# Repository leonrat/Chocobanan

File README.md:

# Chocobanan
An alice-like 40% split keyboard

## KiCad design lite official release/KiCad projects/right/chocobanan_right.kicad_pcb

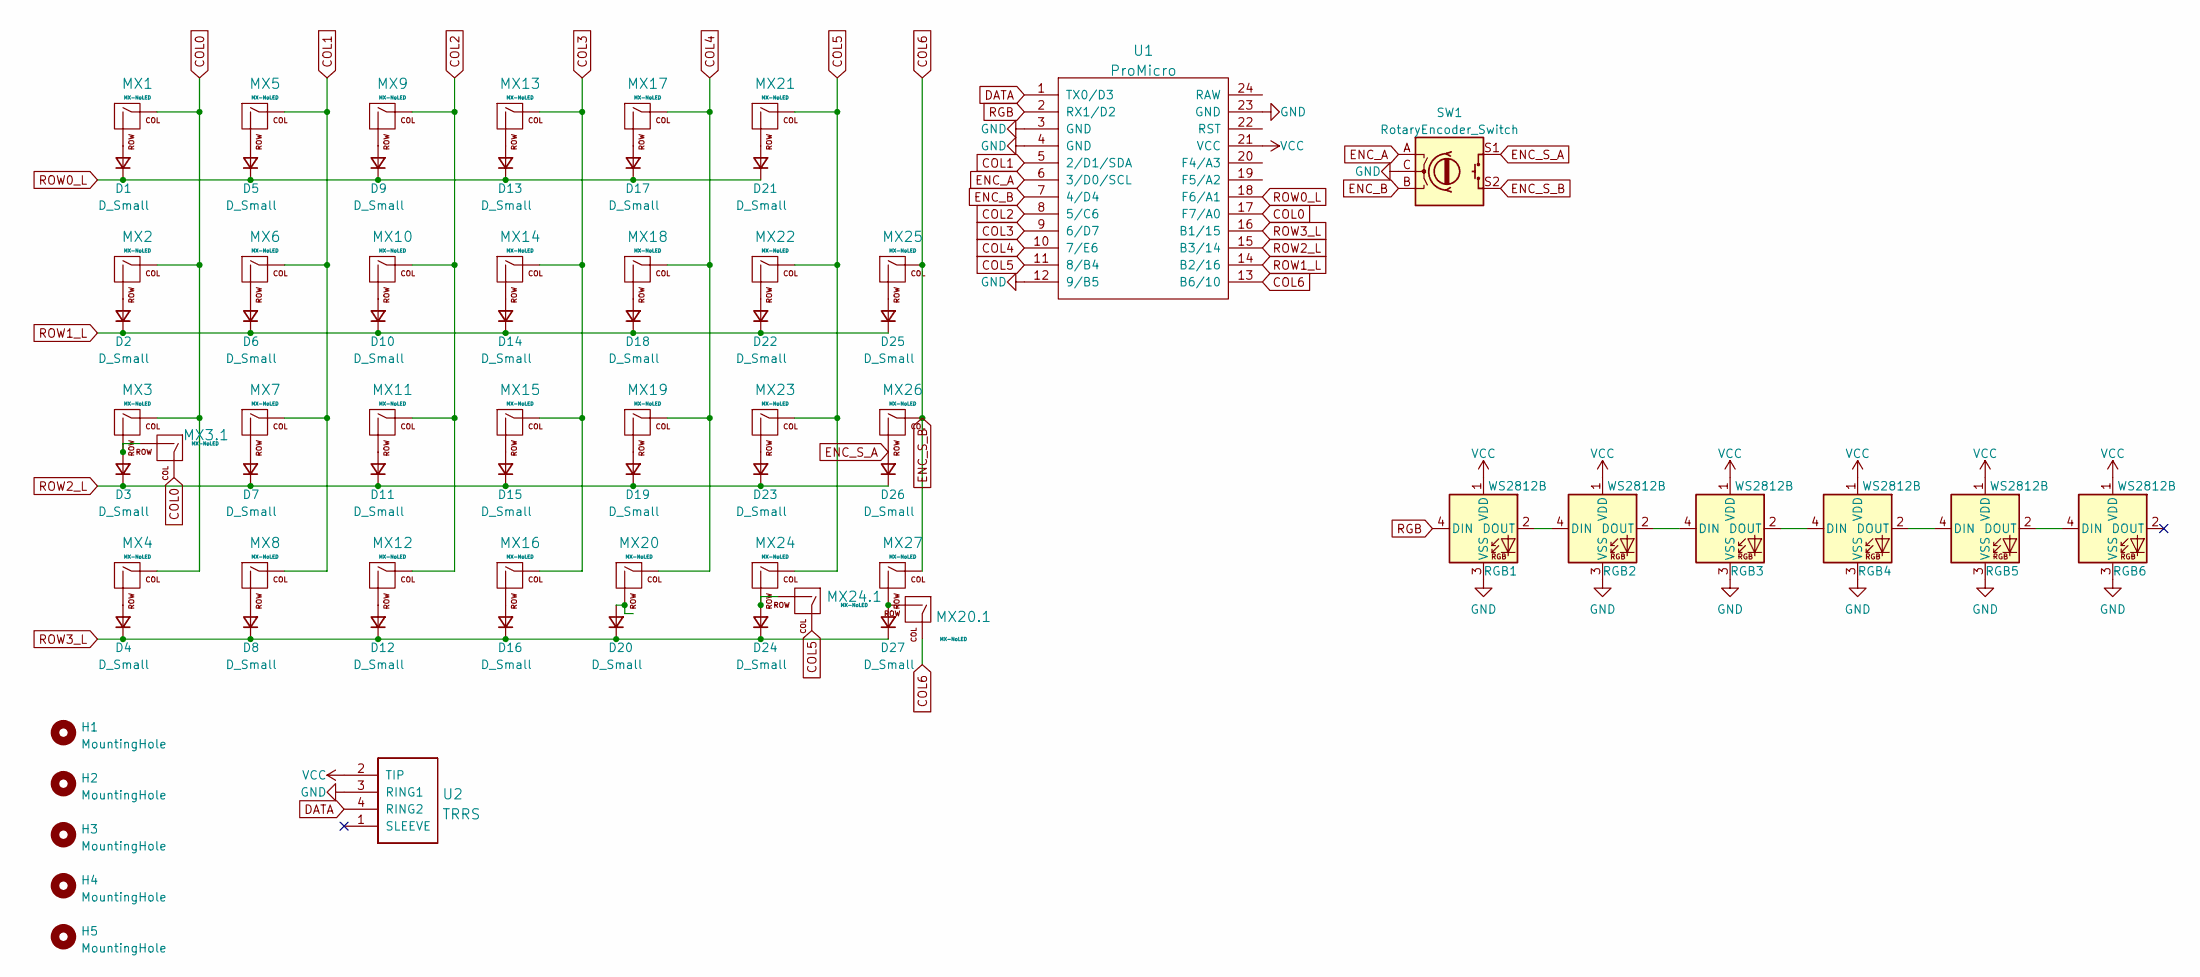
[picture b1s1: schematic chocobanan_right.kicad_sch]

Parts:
D1, D2, D3, D4, D5, D6, D7, D8, D9, D10, D11, D12, D13, D14, D15, D16, D17, D18, D19, D20, D21, D22, D23, D24, D25, D26, D27: D_Small; D3_TH_SMD_only_back
H1, H2, H3, H4, H5: MountingHole; MountingHole_2.1mm
MX1, MX20.1: MX-NoLED; MXOnly-2U-NoLED
MX2: MX-NoLED; MXOnly-2.25U-NoLED
MX3, MX24: MX-NoLED; MXOnly-1.75U-NoLED
MX3.1: MX-NoLED; MXOnly-2.75U-NoLED
MX4: MX-NoLED; MXOnly-1.25U-NoLED
MX5, MX6, MX7, MX8, MX9, MX10, MX11, MX12, MX13, MX14, MX15, MX16, MX17, MX18, MX19, MX20, MX21, MX22, MX23, MX25, MX26, MX27: MX-NoLED; MXOnly-1U-NoLED
MX24.1: MX-NoLED; MXOnly-2.75U-ReversedStabilizers-NoLED
RGB1, RGB2, RGB3, RGB4, RGB5, RGB6: WS2812B; LED_WS2812B-PLCC4
SW1: RotaryEncoder_Switch; RotaryEncoder_EC11_Switch
U1: ProMicro; ArduinoProMicro_centered
U2: TRRS; TRRS-PJ-320A

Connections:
COL0: MX1.1 (COL), MX2.1 (COL), MX3.1 (COL), MX3.1.1 (COL), MX4.1 (COL), U1.17 (F7/A0)
COL1: MX5.1 (COL), MX6.1 (COL), MX7.1 (COL), MX8.1 (COL), U1.5 (2/D1/SDA)
COL2: MX9.1 (COL), MX10.1 (COL), MX11.1 (COL), MX12.1 (COL), U1.8 (5/C6)
COL3: MX13.1 (COL), MX14.1 (COL), MX15.1 (COL), MX16.1 (COL), U1.9 (6/D7)
COL4: MX17.1 (COL), MX18.1 (COL), MX19.1 (COL), MX20.1 (COL), U1.10 (7/E6)
COL5: MX21.1 (COL), MX22.1 (COL), MX23.1 (COL), MX24.1 (COL), MX24.1.1 (COL), U1.11 (8/B4)
COL6: MX20.1.1 (COL), MX25.1 (COL), MX26.1 (COL), MX27.1 (COL), SW1.S2, U1.13 (B6/10)
DATA: U1.1 (TX0/D3), U2.4 (RING2)
ENC_A: SW1.A, U1.6 (3/D0/SCL)
ENC_B: SW1.B, U1.7 (4/D4)
ENC_S_A: D26.2 (A), MX26.2 (ROW), SW1.S1
GND: RGB1.3 (VSS), RGB2.3 (VSS), RGB3.3 (VSS), RGB4.3 (VSS), RGB5.3 (VSS), RGB6.3 (VSS), SW1.C, U1.3 (GND), U1.4 (GND), U1.12 (9/B5), U1.23 (GND), U2.3 (RING1)
unnamed: D1.2 (A), MX1.2 (ROW)
unnamed: D2.2 (A), MX2.2 (ROW)
unnamed: D3.2 (A), MX3.2 (ROW), MX3.1.2 (ROW)
unnamed: D4.2 (A), MX4.2 (ROW)
unnamed: D5.2 (A), MX5.2 (ROW)
unnamed: D6.2 (A), MX6.2 (ROW)
unnamed: D7.2 (A), MX7.2 (ROW)
unnamed: D8.2 (A), MX8.2 (ROW)
unnamed: D9.2 (A), MX9.2 (ROW)
unnamed: D10.2 (A), MX10.2 (ROW)
unnamed: D11.2 (A), MX11.2 (ROW)
unnamed: D12.2 (A), MX12.2 (ROW)
unnamed: D13.2 (A), MX13.2 (ROW)
unnamed: D14.2 (A), MX14.2 (ROW)
unnamed: D15.2 (A), MX15.2 (ROW)
unnamed: D16.2 (A), MX16.2 (ROW)
unnamed: D17.2 (A), MX17.2 (ROW)
unnamed: D18.2 (A), MX18.2 (ROW)
unnamed: D19.2 (A), MX19.2 (ROW)
unnamed: D20.2 (A), MX20.2 (ROW)
unnamed: D21.2 (A), MX21.2 (ROW)
unnamed: D22.2 (A), MX22.2 (ROW)
unnamed: D23.2 (A), MX23.2 (ROW)
unnamed: D24.2 (A), MX24.2 (ROW), MX24.1.2 (ROW)
unnamed: D25.2 (A), MX25.2 (ROW)
unnamed: D27.2 (A), MX20.1.2 (ROW), MX27.2 (ROW)
unnamed: RGB1.2 (DOUT), RGB2.4 (DIN)
unnamed: RGB2.2 (DOUT), RGB3.4 (DIN)
unnamed: RGB3.2 (DOUT), RGB4.4 (DIN)
unnamed: RGB4.2 (DOUT), RGB5.4 (DIN)
unnamed: RGB5.2 (DOUT), RGB6.4 (DIN)
RGB: RGB1.4 (DIN), U1.2 (RX1/D2)
ROW0_L: D1.1 (K), D5.1 (K), D9.1 (K), D13.1 (K), D17.1 (K), D21.1 (K), U1.18 (F6/A1)
ROW1_L: D2.1 (K), D6.1 (K), D10.1 (K), D14.1 (K), D18.1 (K), D22.1 (K), D25.1 (K), U1.14 (B2/16)
ROW2_L: D3.1 (K), D7.1 (K), D11.1 (K), D15.1 (K), D19.1 (K), D23.1 (K), D26.1 (K), U1.15 (B3/14)
ROW3_L: D4.1 (K), D8.1 (K), D12.1 (K), D16.1 (K), D20.1 (K), D24.1 (K), D27.1 (K), U1.16 (B1/15)
VCC: RGB1.1 (VDD), RGB2.1 (VDD), RGB3.1 (VDD), RGB4.1 (VDD), RGB5.1 (VDD), RGB6.1 (VDD), U1.21 (VCC), U2.2 (TIP)

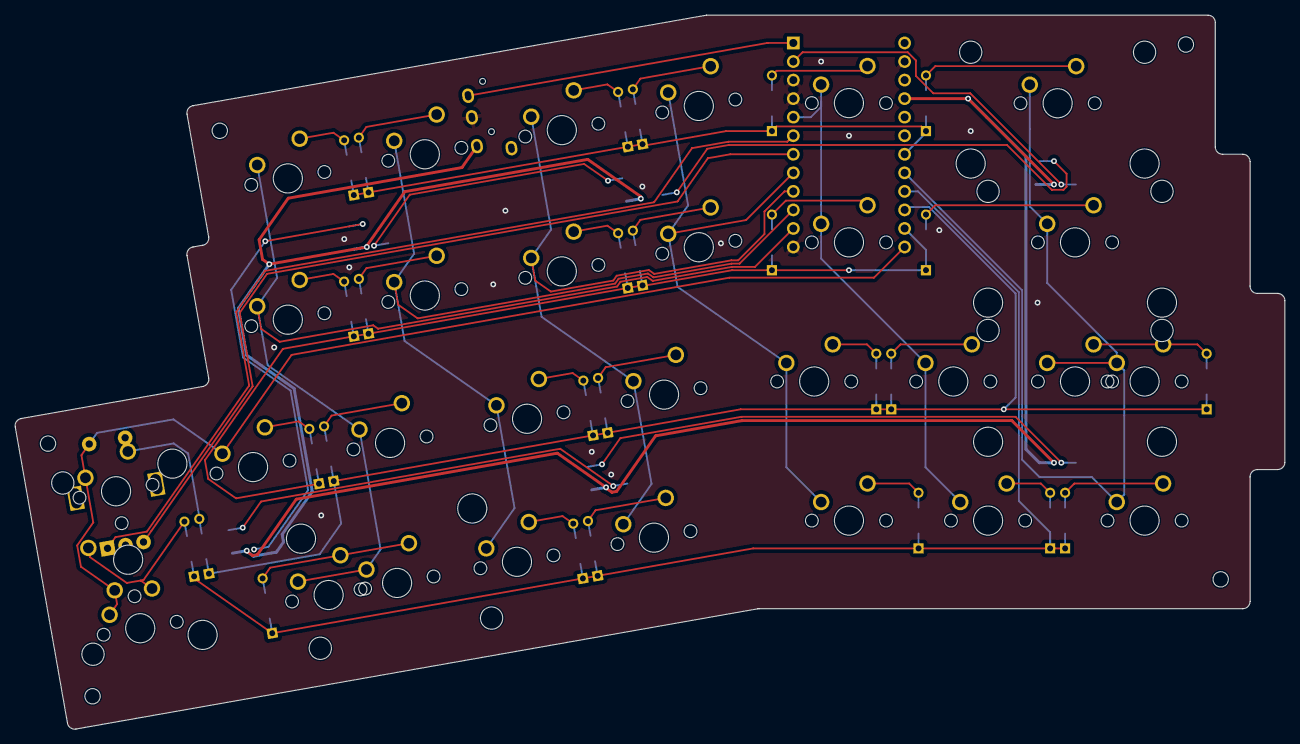
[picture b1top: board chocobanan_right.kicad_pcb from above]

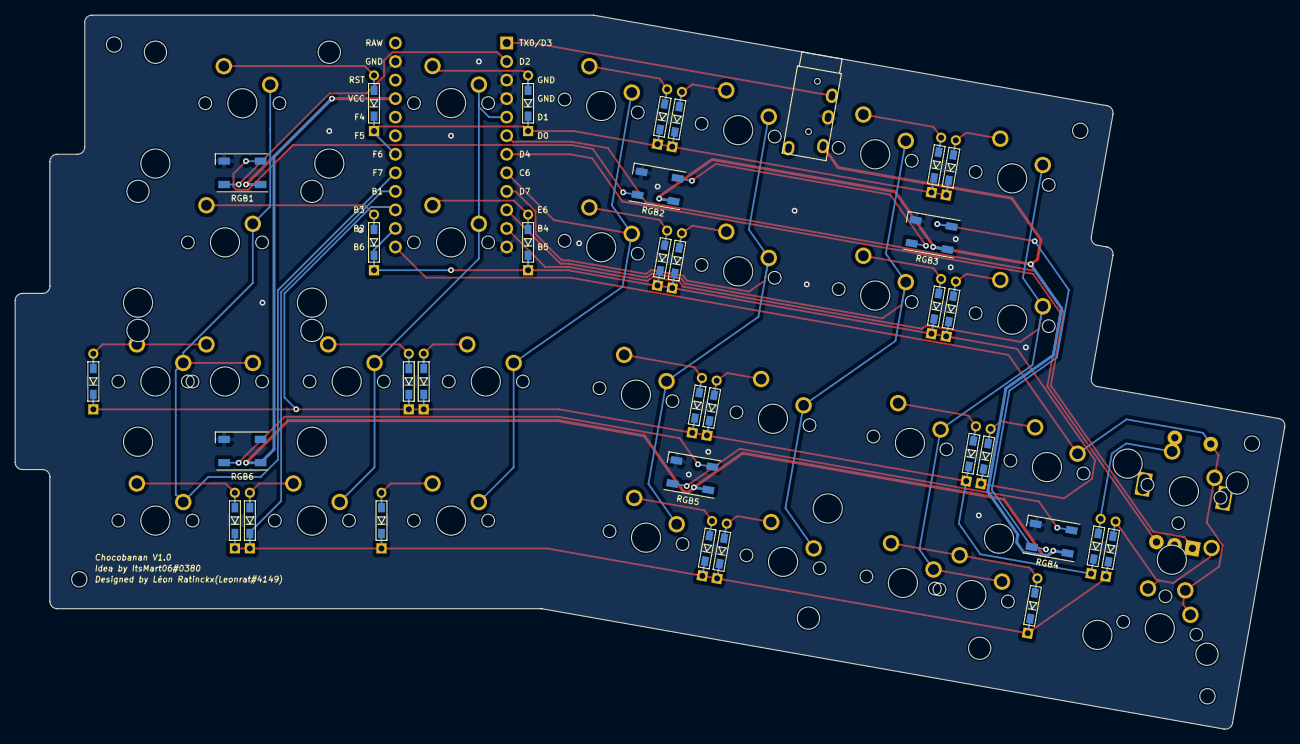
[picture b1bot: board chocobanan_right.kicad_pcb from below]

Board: 2 copper layers, 173.9 x 97.8 mm, 71 parts (12 on the bottom side), 49 nets.

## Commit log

2022-07-23 cloning previous project, and renaming files
2022-07-23 removing unneeded files
2022-07-29 start pcb
2022-08-26 acidentall screenshots, cleanup required
2022-08-30 clean up and technical drawings pcb
2022-09-16 restart project
2022-09-16 cleanup for restart
2022-09-16 cleanup
2022-09-16 restart schematic
2023-04-02 safety push
2023-05-13 clean up
2023-07-31 changes to make sure repo up to date for new pc
2023-10-20 safety commit
2024-02-25 addition project files
2024-02-25 production and project files
2024-02-29 updated gnd fill
2024-08-12 preparing for pc swap
